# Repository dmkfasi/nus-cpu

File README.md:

# nus-cpu

This is my own yet another attempt to re-create Nintendo 64 motherboard for a portable, tablet or bartop mod.

I am going after for as much as possible: modular design, reuse of original components, cheapest production costs and the best visual display picture.

There are many bright minds out there whose ideas I try to adopt and develop further. But since I lack of expertise on several electronics topics, this whole thing definately will need some tune up.

Feel free to use, share and modify!

# Work in progress
Schematics is not verified so far, but it looks complete and legit and came from a more or less reliable source off a retrogaming community board. Everything has been broken down into following components:
* CPU-RCP defines core:
    * CPU to RCP connections;
    * RCP to PIF (Nintendo peripherials controller);
    * PIF to Controller Pak;
    * Power rails, ENABLE delay and /COLDRESET circuit, decoupling capacitors;
    * and breakout connections to external peripherial devices:
        * Gamepak port, 50pin;
        * RDRAM interface, 30pin;
        * Audio DAC, 4pin;
        * Video DAC, 10pin;
        * and Controller pak (two players), 4pin.
* RCP-RDRAM defines RAM interface:
    * Uses of two or four chips:
        * 2 of RDRAM18;
        * 4 of RDRAM18;
        * 2 of RDRAM36.
    * and onboard MX8330 clock generator;
* RCP-CART defines Gamepak interface, simple board with flat cable connector;
* RCP-SND defines audio output interface, either usage of B9480F or any other DAC and amplifier;
* RCP-VDC will define video interface.

# PCB design and production files
* CPU-RCP is 4 layer board, finished, Gerber files are included;

* RCP-RDRAM is 4 layer board, finished, Gerber files are included;

* RCP-CART is 2 layer board, finished, Gerber files are included;

* RCP-SND is not started yet;
* RCP-VDC is not started yet;

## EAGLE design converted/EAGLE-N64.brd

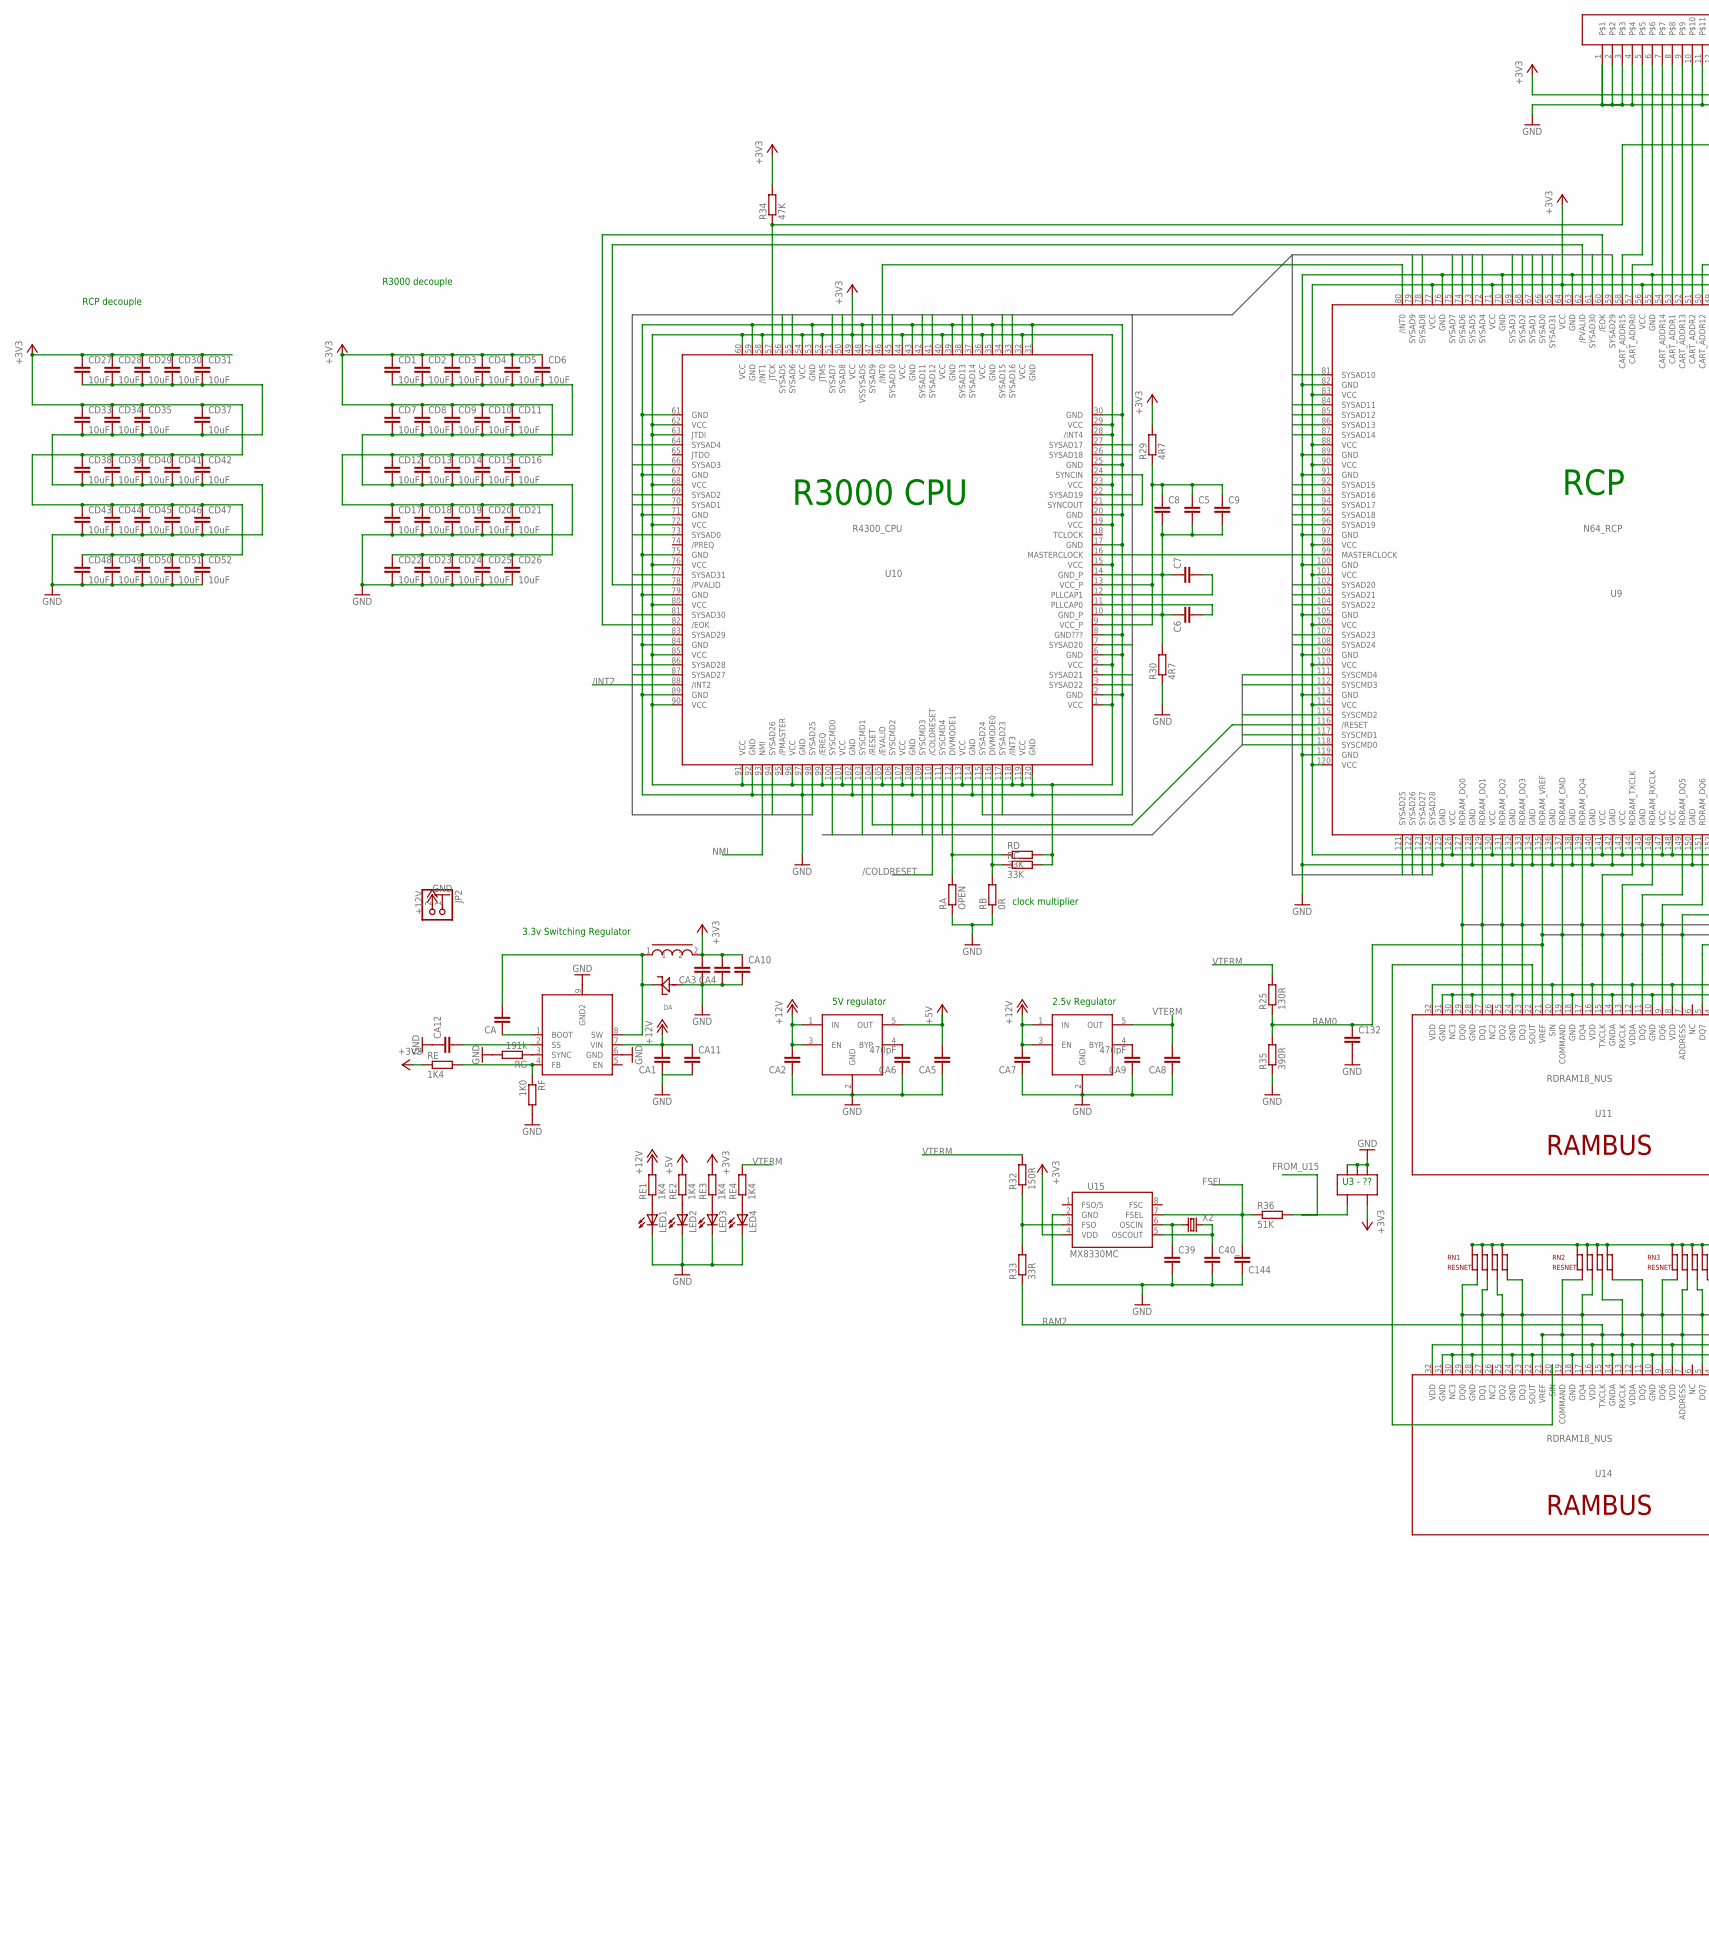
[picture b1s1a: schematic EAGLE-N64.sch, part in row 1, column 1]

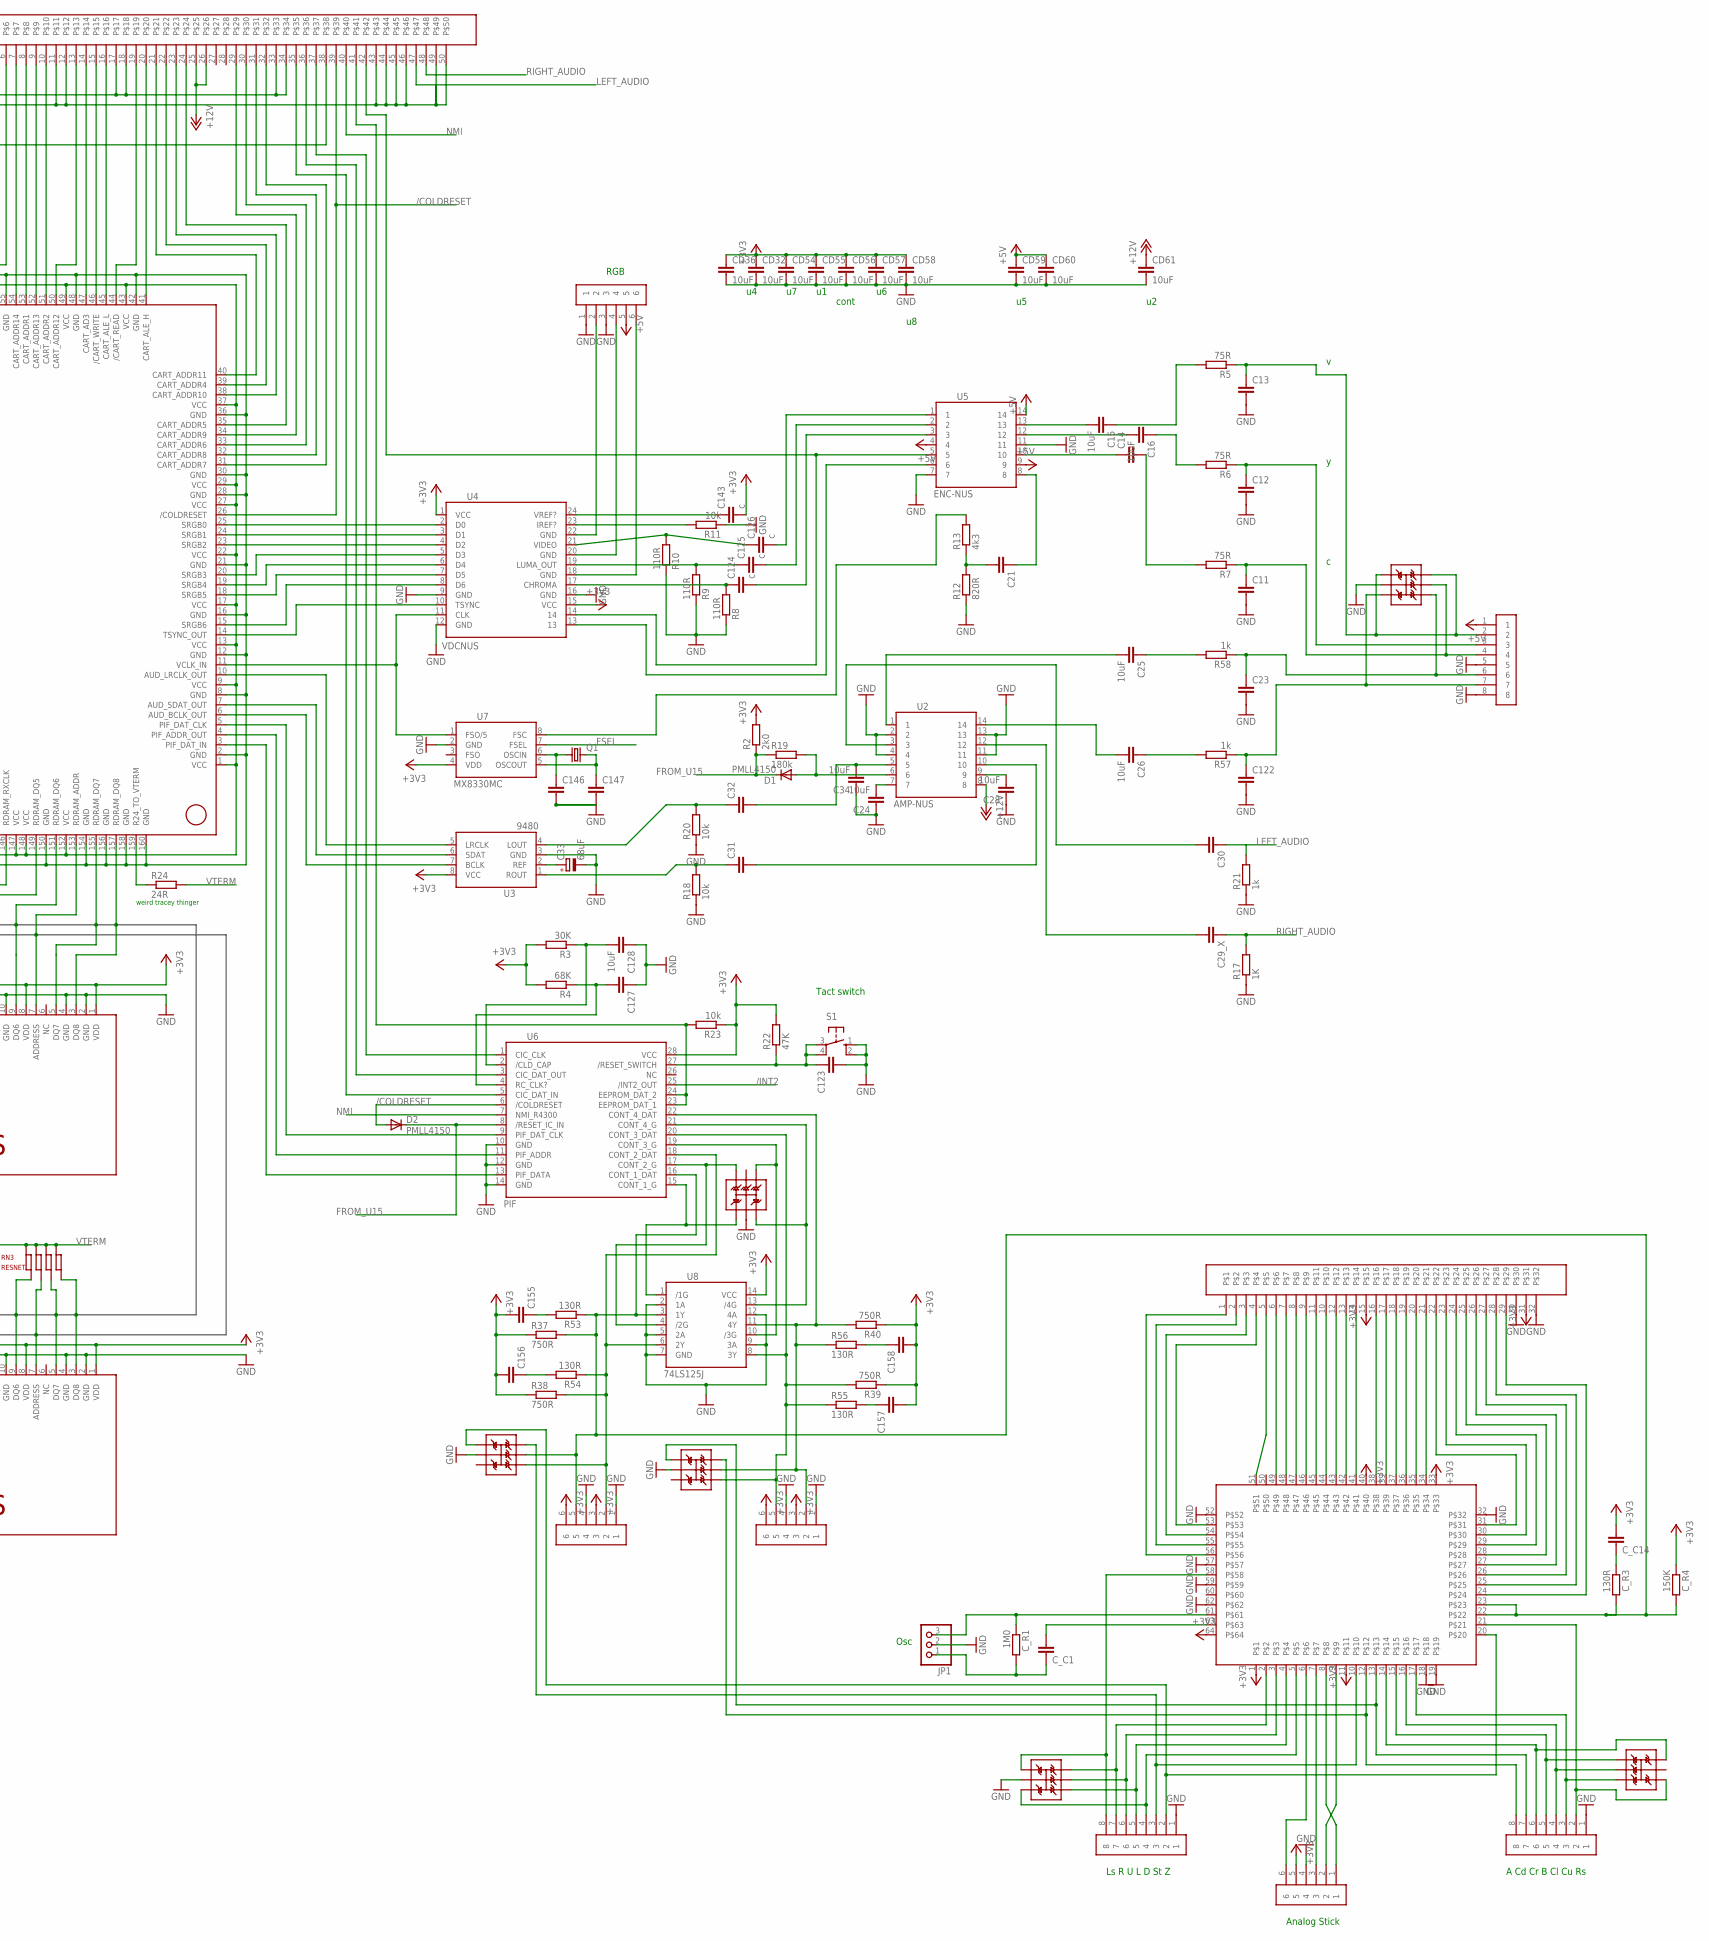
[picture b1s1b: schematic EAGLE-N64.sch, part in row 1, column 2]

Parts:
3V3: LM22680; PSOP-8
AV: PINHEAD-1X8; 2MMPINHEAD-1X8
BUTT1, BUTT2: PINHEAD-1X8; 2MMPINHEAD-1X8
C5: C-EUC0805K; C0805K
C6, C7, C8, C9, C11, C12, C13, C14, C21, C23, C29_X, C30, C31, C32, C39, C40_, C122, C123, C127, C132, C144, C146, C147, C155, C156, C157, C158: C-EUC0805; C0805
C15, C16, C24, C25, C26, C28, C34, C128: 10uF; C0805
C33: 68uF; C/6032-28R
C124, C125, C126, C143: c; C0805
CA, CA1, CA4: C-EUC1206K; C1206K
CA2, CA5, CA7, CA8, CA10, CA11, CA12: C-EUC0805K; C0805K
CA3: C-EUC1210K; C1210K
CA6, CA9: 470pF; C0805K
CD1, CD2, CD3, CD4, CD5, CD6, CD7, CD8, CD9, CD10, CD11, CD12, CD13, CD14, CD15, CD16, CD17, CD18, CD19, CD20, CD21, CD22, CD23, CD24, CD25, CD26, CD27, CD28, CD29, CD30, CD31, CD32, CD33, CD34, CD35, CD36, CD37, CD38, CD39, CD40, CD41, CD42, CD43, CD44, CD45, CD46, CD47, CD48, CD49, CD50, CD51, CD52, CD54, CD55, CD56, CD57, CD58, CD59, CD60, CD61: 10uF; C0805
CONT1, CONT2: PINHEAD-1X6; 2MMPINHEAD-1X6
C_C1, C_C14: C-EUC0805; C0805
C_R1: 1M0; M0805
C_R3: 130R; M0805
C_R4: 150K; M0805
C_U1: CNT-NUS; PQFP64
D1, D2: PMLL4150; SOD80C
DA: STKYDIODE
JOY: PINHEAD-1X6; 2MMPINHEAD-1X6
JP1: PINHD-1X3; 1X03
JP2: PINHD-1X2; 1X02
LED1, LED2, LED3, LED4: LEDCHIPLED_0805; CHIPLED_0805
Q1: CRYTALHC49S; HC49/S
R2: 2k0; M0805
R3: 30K; M0805
R4: 68K; M0805
R5, R6, R7: 75R; M0805
R8, R9, R10: 110R; M0805
R11, R18, R20, R23: 10k; M0805
R12: 820R; M0805
R13: 4k3; M0805
R17: 1K; M0805
R19: 180k; M0805
R21, R57, R58: 1k; M0805
R22, R34: 47K; M0805
R24: 24R; M0805
R25, R53, R54, R55, R56: 130R; M0805
R29, R30: 4R7; M0805
R32: 150R; M0805
R33: 33R; M0805
R35: 390R; M0805
R36: 51K; M0805
R37, R38, R39, R40: 750R; M0805
RA: OPEN; M0805
RB: 0R; M0805
RC: 33K; M0805
RD: 33K; M0805
RE, RE1, RE2, RE3, RE4: 1K4; M0805
RF: 1K0; M0805
RG: 191k; M0805
RGB: PINHEAD-1X6; 2MMPINHEAD-1X6
RN1, RN2, RN3: RESNET; RESARRAY
S1: 10-XX; B3F-10XX
TVS1, TVS2, TVS3, TVS4, TVS5, TVS6: TVS; SC-74
U2: AMP-NUS; SO14
U3: 9480; SO8
U3_: U3; SOT23-5
U4: VDCNUS; SO24
U5: ENC-NUS; SO14
U6: PIF; SO28W
U7, U15: MX8330MC; SO08
U8: 74LS125J; QSOP14
U9: N64_RCP; PQFP160
U10: R4300_CPU; QFP120
U11, U14: RDRAM18_NUS; SHP32
U12, U13: MIC5219; SOT23-5
U$37: PINHEAD-25X2
U$38: PINHEAD-16X2SMALLER; 2MMPINHEAD-16X2
U$52: INDUCTOR
X2: CRYTALHC49S; HC49/S

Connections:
3V3: C143.2, C155.2, C156.2, C157.2, C158.2, CA3.2, CA4.2, CA10.1, CD1.1, CD2.1, CD3.1, CD4.1, CD5.1, CD6.1, CD7.1, CD8.1, CD9.1, CD10.1, CD11.1, CD12.1, CD13.1, CD14.1, CD15.1, CD16.1, CD17.1, CD18.1, CD19.1, CD20.1, CD21.1, CD22.1, CD23.1, CD24.1, CD25.1, CD26.1, CD27.1, CD28.1, CD29.1, CD30.1, CD31.1, CD32.1, CD33.1, CD34.1, CD35.1, CD36.1, CD37.1, CD38.1, CD39.1, CD40.1, CD41.1, CD42.1, CD43.1, CD44.1, CD45.1, CD46.1, CD47.1, CD48.1, CD49.1, CD50.1, CD51.1, CD52.1, CD54.1, CD55.1, CD56.1, CD57.1, CD58.1, CONT1.3, CONT1.6, CONT2.3, CONT2.6, C_C14.2, C_R4.1, C_U1.1, C_U1.11, C_U1.33, C_U1.40, C_U1.64, JOY.5, R2.2, R3.2, R4.2, R22.2, R23.1, R29.2, R34.2, R37.1, R38.1, R39.1, R40.1, RC.2, RD.2, RE.1, RE3.2, U3.8 (VCC), U3_.5, U4.1 (VCC), U4.15 (VCC), U6.28 (VCC), U7.4 (VDD), U8.14 (VCC), U9.1 (VCC), U9.9 (VCC), U9.13 (VCC), U9.17 (VCC), U9.22 (VCC), U9.27 (VCC), U9.29 (VCC), U9.37 (VCC), U9.43 (VCC), U9.49 (VCC), U9.56 (VCC), U9.64 (VCC), U9.71 (VCC), U9.77 (VCC), U9.83 (VCC), U9.88 (VCC), U9.90 (VCC), U9.98 (VCC), U9.101 (VCC), U9.106 (VCC), U9.110 (VCC), U9.114 (VCC), U9.120 (VCC), U9.126 (VCC), U9.130 (VCC), U9.141 (VCC), U9.143 (VCC), U9.147 (VCC), U9.148 (VCC), U9.152 (VCC), U10.1 (VCC), U10.5 (VCC), U10.15 (VCC), U10.19 (VCC), U10.23 (VCC), U10.28 (/INT4), U10.29 (VCC), U10.32 (VCC), U10.36 (VCC), U10.40 (VCC), U10.44 (VCC), U10.49 (VCC), U10.52 (JTMS), U10.54 (VCC), U10.58 (/INT1), U10.60 (VCC), U10.62 (VCC), U10.63 (JTDI), U10.68 (VCC), U10.72 (VCC), U10.76 (VCC), U10.80 (VCC), U10.85 (VCC), U10.90 (VCC), U10.91 (VCC), U10.96 (VCC), U10.99 (/EREQ), U10.101 (VCC), U10.105 (/EVALID), U10.107 (VCC), U10.113 (VCC), U10.118 (/INT3), U10.119 (VCC), U11.1 (VDD), U11.8 (VDD), U11.12 (VDDA), U11.16 (VDD), U11.20 (SIN), U11.32 (VDD), U14.1 (VDD), U14.8 (VDD), U14.12 (VDDA), U14.16 (VDD), U14.32 (VDD), U15.4 (VDD), U$37.17, U$37.18, U$37.33, U$37.34, U$38.15, U$38.31, U$52.2
+5V: AV.1, CA5.2, CD59.1, CD60.1, RE2.2, RGB.5, U5.4, U5.9, U5.14, U13.5 (OUT)
+12V: 3V3.7 (VIN), CA1.2, CA2.2, CA7.2, CA11.1, CD61.1, JP2.2, RE1.2, U2.8, U12.1 (IN), U12.3 (EN), U13.1 (IN), U13.3 (EN), U$37.25, U$37.26
/COLDRESET: D2.A, U6.6 (/COLDRESET), U9.26 (/COLDRESET), U10.110 (/COLDRESET), U$37.39
/INT2: U6.25 (/INT2_OUT), U10.88 (/INT2)
ADJ: 3V3.4 (FB), RE.2, RF.1
C16X: C16.1, R6.2
C_C11: C_C1.1, C_R1.2, JP1.1
DQ0: RN1.1, U9.127 (RDRAM_DQ0), U11.29 (DQ0), U14.29 (DQ0)
DQ1: RN1.2, U9.129 (RDRAM_DQ1), U11.27 (DQ1), U14.27 (DQ1)
DQ2: RN1.3, U9.131 (RDRAM_DQ2), U11.25 (DQ2), U14.25 (DQ2)
DQ3: RN1.4, U9.133 (RDRAM_DQ3), U11.23 (DQ3), U14.23 (DQ3)
DQ4: RN2.2, U9.139 (RDRAM_DQ4), U11.17 (DQ4), U14.17 (DQ4)
DQ5: RN2.4, U9.149 (RDRAM_DQ5), U11.11 (DQ5), U14.11 (DQ5)
DQ6: RN3.1, U9.151 (RDRAM_DQ6), U11.9 (DQ6), U14.9 (DQ6)
DQ7: RN3.3, U9.155 (RDRAM_DQ7), U11.5 (DQ7), U14.5 (DQ7)
DQ8: RN3.4, U9.157 (RDRAM_DQ8), U11.3 (DQ8), U14.3 (DQ8)
FROM_U15: D1.C, D2.C, R2.1, R19.1, R36.2, U3_.4, U6.8 (/RESET_IC_IN)
FSEL: C144.2, R36.1, U7.7 (FSEL), U15.7 (FSEL)
FSO1: R32.1, R33.2, U15.3 (FSO)
GND: 3V3.6 (GND), 3V3.9 (GND2), AV.5, AV.8, BUTT1.1, BUTT2.1, C11.2, C12.2, C13.2, C23.2, C24.1, C28.1, C33.-, C34.1, C39.2, C40_.2, C122.2, C123.2, C127.1, C128.1, C132.2, C144.1, C146.2, C147.2, CA1.1, CA2.1, CA3.1, CA4.1, CA5.1, CA6.1, CA7.1, CA8.1, CA9.1, CA10.2, CA11.2, CA12.1, CD1.2, CD2.2, CD3.2, CD4.2, CD5.2, CD6.2, CD7.2, CD8.2, CD9.2, CD10.2, CD11.2, CD12.2, CD13.2, CD14.2, CD15.2, CD16.2, CD17.2, CD18.2, CD19.2, CD20.2, CD21.2, CD22.2, CD23.2, CD24.2, CD25.2, CD26.2, CD27.2, CD28.2, CD29.2, CD30.2, CD31.2, CD32.2, CD33.2, CD34.2, CD35.2, CD36.2, CD37.2, CD38.2, CD39.2, CD40.2, CD41.2, CD42.2, CD43.2, CD44.2, CD45.2, CD46.2, CD47.2, CD48.2, CD49.2, CD50.2, CD51.2, CD52.2, CD54.2, CD55.2, CD56.2, CD57.2, CD58.2, CD59.2, CD60.2, CD61.2, CONT1.1, CONT1.4, CONT2.1, CONT2.4, C_U1.18, C_U1.19, C_U1.32, C_U1.52, C_U1.57, C_U1.59, C_U1.62, DA.+, JOY.4, JP1.2, JP2.1, LED1.C, LED2.C, LED3.C, LED4.C, R8.1, R9.1, R10.1, R11.1, R12.1, R17.1, R18.1, R20.1, R21.1, R30.1, R35.1, RA.1, RB.1, RF.2, RG.2, RGB.1, RGB.3, S1.1 (S), S1.2 (S1), TVS1.2, TVS2.2, TVS3.2, TVS4.2, TVS5.2, U2.2, U2.4, U2.11, U2.13, U3.3 (GND), U3_.1, U3_.2, U3_.3, U4.9 (GND), U4.12 (GND), U4.16 (GND), U5.7, U5.11, U6.10 (GND), U6.12 (GND), U6.14 (GND), U7.2 (GND), U8.2 (1A), U8.5 (2A), U8.7 (GND), U8.9 (3A), U8.12 (4A), U9.2 (GND), U9.8 (GND), U9.12 (GND), U9.16 (GND), U9.21 (GND), U9.28 (GND), U9.30 (GND), U9.36 (GND), U9.42 (GND), U9.48 (GND), U9.55 (GND), U9.63 (GND), U9.70 (GND), U9.76 (GND), U9.82 (GND), U9.89 (GND), U9.91 (GND), U9.97 (GND), U9.100 (GND), U9.105 (GND), U9.109 (GND), U9.113 (GND), U9.119 (GND), U9.125 (GND), U9.128 (GND), U9.132 (GND), U9.134 (GND), U9.136 (GND), U9.138 (GND)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
INT0: U9.80 (/INT0), U10.46 (/INT0)
LEFT_AUDIO: C30.1, R21.2, U$37.47
unnamed: C156.1, R54.2
unnamed: C155.1, R53.2
unnamed: U4.11 (CLK), U7.1 (FSO/5), U9.11 (VCLK_IN)
unnamed: R24.1, U9.159 (R24_TO_VTERM)
unnamed: C147.1, Q1.2, U7.5 (OSCOUT)
unnamed: C146.1, Q1.1, U7.6 (OSCIN)
unnamed: BUTT1.2, C_U1.20, TVS3.1
unnamed: RGB.2, U4.22 (GND)
unnamed: RGB.4, U4.20 (GND)
unnamed: U6.9 (PIF_DAT_CLK), U9.5 (PIF_DAT_CLK)
unnamed: U6.11 (PIF_ADDR), U9.4 (PIF_ADDR_OUT)
unnamed: U6.13 (PIF_DATA), U9.3 (PIF_DAT_IN)
unnamed: TVS2.1, U6.15 (CONT_1_G), U8.1 (/1G)
unnamed: CONT1.5, C_R3.2, C_R4.2, C_U1.22, C_U1.23, R37.2, R53.1, TVS3.5, U6.16 (CONT_1_DAT), U8.3 (1Y)
unnamed: BUTT1.3, C_U1.10, TVS3.6
unnamed: LED1.A, RE1.1
unnamed: CONT1.2, R38.2, R54.1, TVS3.4, U6.18 (CONT_2_DAT), U8.6 (2Y)
unnamed: TVS2.4, U6.19 (CONT_3_G), U8.10 (/3G)
unnamed: CONT2.5, R39.2, R55.1, TVS4.4, U6.20 (CONT_3_DAT), U8.8 (3Y)
unnamed: TVS2.3, U6.21 (CONT_4_G), U8.13 (/4G)
unnamed: CONT2.2, R40.2, R56.1, TVS4.5, U6.22 (CONT_4_DAT), U8.11 (4Y)
unnamed: U4.2 (D0), U9.25 (SRGB0)
unnamed: U9.116 (/RESET), U10.104 (/RESET)
unnamed: TVS2.6, U6.17 (CONT_2_G), U8.4 (/2G)
unnamed: U9.62 (/PVALID), U10.78 (/PVALID)
unnamed: U9.60 (/EOK), U10.82 (/EOK)
unnamed: C123.1, R22.1, S1.3, S1.4 (P1), U6.27 (/RESET_SWITCH)
unnamed: U4.3 (D1), U9.24 (SRGB1)
unnamed: RB.2, RC.1, U10.116 (DIVMODE0)
unnamed: U9.39 (CART_ADDR4), U$37.22
unnamed: RA.2, RD.1, U10.112 (DIVMODE1)
unnamed: U9.58 (CART_ADDR15), U$37.5
unnamed: U9.57 (CART_ADDR0), U$37.6
unnamed: U9.54 (CART_ADDR14), U$37.7
unnamed: U9.53 (CART_ADDR1), U$37.8
unnamed: U9.52 (CART_ADDR13), U$37.9
unnamed: U9.51 (CART_ADDR2), U$37.10
unnamed: U9.99 (MASTERCLOCK), U10.16 (MASTERCLOCK)
unnamed: U9.50 (CART_ADDR12), U$37.13
unnamed: U9.47 (CART_AD3), U$37.14
unnamed: U9.46 (/CART_WRITE), U$37.15
unnamed: U9.45 (CART_ALE_L), U$37.16
unnamed: U9.44 (/CART_READ), U$37.19
unnamed: U9.41 (CART_ALE_H), U$37.20
unnamed: U9.38 (CART_ADDR10), U$37.23
unnamed: U9.35 (CART_ADDR5), U$37.24
unnamed: U9.34 (CART_ADDR9), U$37.29
unnamed: U9.33 (CART_ADDR6), U$37.30
unnamed: U9.32 (CART_ADDR8), U$37.31
unnamed: U9.31 (CART_ADDR7), U$37.32
unnamed: C157.1, R55.2
unnamed: U6.5 (CIC_DAT_IN), U$37.35
unnamed: U6.3 (CIC_DAT_OUT), U$37.36
unnamed: U6.1 (CIC_CLK), U$37.37
unnamed: R23.2, U6.23 (EEPROM_DAT_1), U6.24 (EEPROM_DAT_2), U$37.41
unnamed: C5.1, C8.1, C9.1, R29.1, U10.9 (VCC_P), U10.13 (VCC_P)
unnamed: C5.2, C6.1, C7.1, C8.2, C9.2, R30.2, U10.10 (GND_P), U10.14 (GND_P)
unnamed: C6.2, U10.11 (PLLCAP0)
unnamed: C7.2, U10.12 (PLLCAP1)
unnamed: U10.21 (SYNCOUT), U10.24 (SYNCIN)
unnamed: U3.5 (LRCLK), U9.10 (AUD_LRCLK_OUT)
unnamed: U3.6 (SDAT), U9.7 (AUD_SDAT_OUT)
unnamed: U3.7 (BCLK), U9.6 (AUD_BCLK_OUT)
unnamed: C33.+, U3.2 (REF)
unnamed: C127.2, R4.1, U6.4 (RC_CLK?)
unnamed: C128.2, R3.1, U6.2 (/CLD_CAP)
unnamed: U4.4 (D2), U9.23 (SRGB2)
unnamed: U4.5 (D3), U9.20 (SRGB3)
unnamed: U4.6 (D4), U9.19 (SRGB4)
unnamed: U4.7 (D5), U9.18 (SRGB5)
unnamed: U4.8 (D6), U9.15 (SRGB6)
unnamed: U4.10 (TSYNC), U9.14 (TSYNC_OUT)
unnamed: R11.2, U4.23 (IREF?)
unnamed: C126.1, R10.2, U4.21 (VIDEO)
unnamed: R34.1, U10.57 (JTCK), U$37.38
unnamed: C32.1, R20.2, U3.4 (LOUT)
unnamed: C31.1, R18.2, U3.1 (ROUT)
unnamed: C143.1, U4.24 (VREF?)
unnamed: C125.1, R9.2, U4.19 (LUMA_OUT)
unnamed: C124.1, R8.2, U4.17 (CHROMA)
unnamed: C158.1, R56.2
unnamed: C32.2, C34.2, U2.5
unnamed: C31.2, U2.10
unnamed: C24.2, U2.7
unnamed: C28.2, U2.9
unnamed: C29_X.2, U2.12
unnamed: C30.2, U2.3
unnamed: D1.A, R19.2, U2.6
unnamed: C25.1, R58.2
unnamed: C14.1, U5.10
unnamed: C26.2, U2.14
unnamed: AV.7, C122.1, R57.1, TVS1.3
unnamed: C26.1, R57.2
unnamed: C_U1.56, U$38.1
unnamed: CA6.2, U13.4 (BYP)
unnamed: C_U1.55, U$38.2
unnamed: U4.13, U5.6
unnamed: U4.14, U5.5, U$37.42
unnamed: C124.2, U5.3
unnamed: C125.2, U5.2
unnamed: C126.2, U5.1
unnamed: C15.1, R5.2
unnamed: C15.2, U5.13
unnamed: C16.2, U5.12
unnamed: AV.4, C11.1, R7.1, TVS1.5
unnamed: AV.3, C12.1, R6.1
unnamed: C14.2, R7.2
unnamed: C21.1, U5.8
unnamed: R13.2, U7.8 (FSC)
unnamed: C21.2, R12.2, R13.1
unnamed: AV.2, C13.1, R5.1, TVS1.1, TVS1.6
unnamed: RGB.6, U4.18 (GND)
unnamed: C_U1.8, JOY.1
unnamed: C_U1.54, U$38.3
unnamed: C_U1.53, U$38.4
unnamed: C_U1.9, JOY.2
unnamed: C_U1.51, U$38.5
unnamed: C_U1.49, U$38.6
unnamed: C_U1.48, U$38.7
unnamed: C_U1.47, U$38.8
unnamed: U9.40 (CART_ADDR11), U$37.21
unnamed: C_U1.46, U$38.9
unnamed: C_U1.45, U$38.11
unnamed: C_U1.44, U$38.10
unnamed: C_U1.43, U$38.12
unnamed: C_U1.42, U$38.13
unnamed: C_U1.41, U$38.14
unnamed: BUTT2.2, C_U1.21, TVS6.1
unnamed: C_U1.38, U$38.16
unnamed: C_U1.37, U$38.18
unnamed: C_U1.39, U$38.17
unnamed: C_U1.36, U$38.19
unnamed: C_U1.35, U$38.20
unnamed: C_U1.34, U$38.21
unnamed: C_U1.31, U$38.22
unnamed: C_U1.30, U$38.23
unnamed: C_U1.29, U$38.24
unnamed: C_U1.28, U$38.25
unnamed: C_U1.27, U$38.26
unnamed: C_U1.26, U$38.27
unnamed: C_U1.25, U$38.28
unnamed: C_U1.24, U$38.29
unnamed: C_C14.1, C_R3.1
unnamed: 3V3.2 (SS), CA12.2
unnamed: BUTT2.3, C_U1.17, TVS6.6
unnamed: BUTT2.4, C_U1.16, TVS6.5
unnamed: BUTT2.5, C_U1.15, TVS6.4
unnamed: BUTT2.6, C_U1.14, TVS6.3
unnamed: BUTT2.7, C_U1.13, TVS4.1
unnamed: BUTT2.8, C_U1.12, TVS4.6
unnamed: C_U1.7, JOY.3
unnamed: C_U1.6, JOY.6
unnamed: BUTT1.4, C_U1.5, TVS5.3
unnamed: BUTT1.5, C_U1.4, TVS5.4
unnamed: BUTT1.6, C_U1.3, TVS5.5
unnamed: BUTT1.7, C_U1.2, TVS5.6
unnamed: BUTT1.8, C_U1.58, TVS5.1
unnamed: C_R1.1, C_U1.61, JP1.3
unnamed: C_C1.2, C_U1.63
unnamed: CA9.2, U12.4 (BYP)
unnamed: 3V3.3 (SYNC), RG.1
unnamed: 3V3.1 (BOOT), CA.1
unnamed: LED2.A, RE2.1
unnamed: LED4.A, RE4.1
unnamed: LED3.A, RE3.1
NMI: U6.7 (NMI_R4300), U10.93 (NMI), U$37.40
OSCIN1: C39.1, U15.6 (OSCIN), X2.1
OSCOUT1: C40_.1, U15.5 (OSCOUT), X2.2
R58: AV.6, C23.1, R58.1, TVS1.4
RAM0: C132.1, R25.1, R35.2, U9.135 (RDRAM_VREF), U11.21 (VREF), U14.21 (VREF)
RAM1: RN2.1, U9.137 (RDRAM_CMD), U11.19 (COMMAND), U14.19 (COMMAND)
RAM2: R33.1, U9.144 (RDRAM_TXCLK), U11.15 (TXCLK), U14.15 (TXCLK)
RAM3: RN2.3, U9.146 (RDRAM_RXCLK), U11.13 (RXCLK), U14.13 (RXCLK)
RAM4: RN3.2, U9.153 (RDRAM_ADDR), U11.7 (ADDRESS), U14.7 (ADDRESS)
RIGHT_AUDIO: C29_X.1, R17.2, U$37.48
SW: 3V3.8 (SW), CA.2, DA.-, U$52.1
SYSAD0: U9.66 (SYSAD0), U10.73 (SYSAD0)
SYSAD1: U9.67 (SYSAD1), U10.70 (SYSAD1)
SYSAD2: U9.68 (SYSAD2), U10.69 (SYSAD2)
SYSAD3: U9.69 (SYSAD3), U10.66 (SYSAD3)
SYSAD4: U9.72 (SYSAD4), U10.64 (SYSAD4)
SYSAD5: U9.73 (SYSAD5), U10.56 (SYSAD5)
SYSAD6: U9.74 (SYSAD6), U10.55 (SYSAD6)
SYSAD7: U9.75 (SYSAD7), U10.51 (SYSAD7)
SYSAD8: U9.78 (SYSAD8), U10.50 (SYSAD8)
SYSAD9: U9.79 (SYSAD9), U10.47 (SYSAD9)
SYSAD10: U9.81 (SYSAD10), U10.45 (SYSAD10)
SYSAD11: U9.84 (SYSAD11), U10.42 (SYSAD11)
SYSAD12: U9.85 (SYSAD12), U10.41 (SYSAD12)
SYSAD13: U9.86 (SYSAD13), U10.38 (SYSAD13)
SYSAD14: U9.87 (SYSAD14), U10.37 (SYSAD14)
SYSAD15: U9.92 (SYSAD15), U10.34 (SYSAD15)
SYSAD16: U9.93 (SYSAD16), U10.33 (SYSAD16)
SYSAD17: U9.94 (SYSAD17), U10.27 (SYSAD17)
SYSAD18: U9.95 (SYSAD18), U10.26 (SYSAD18)
SYSAD19: U9.96 (SYSAD19), U10.22 (SYSAD19)
SYSAD20: U9.102 (SYSAD20), U10.7 (SYSAD20)
SYSAD21: U9.103 (SYSAD21), U10.4 (SYSAD21)
SYSAD22: U9.104 (SYSAD22), U10.3 (SYSAD22)
SYSAD23: U9.107 (SYSAD23), U10.117 (SYSAD23)
SYSAD24: U9.108 (SYSAD24), U10.115 (SYSAD24)
SYSAD25: U9.121 (SYSAD25), U10.98 (SYSAD25)
SYSAD26: U9.122 (SYSAD26), U10.94 (SYSAD26)
SYSAD27: U9.123 (SYSAD27), U10.87 (SYSAD27)
SYSAD28: U9.124 (SYSAD28), U10.86 (SYSAD28)
SYSAD29: U9.59 (SYSAD29), U10.83 (SYSAD29)
SYSAD30: U9.61 (SYSAD30), U10.81 (SYSAD30)
SYSAD31: U9.65 (SYSAD31), U10.77 (SYSAD31)
SYSCMD0: U9.118 (SYSCMD0), U10.100 (SYSCMD0)
SYSCMD1: U9.117 (SYSCMD1), U10.103 (SYSCMD1)
SYSCMD2: U9.115 (SYSCMD2), U10.106 (SYSCMD2)
SYSCMD3: U9.112 (SYSCMD3), U10.109 (SYSCMD3)
SYSCMD4: U9.111 (SYSCMD4), U10.111 (SYSCMD4)
U2: C25.2, U2.1
U3: U11.22 (SOUT), U14.20 (SIN)
VTERM: CA8.2, R24.2, R25.2, R32.2, RE4.2, RN1.5, RN1.6, RN1.7, RN1.8, RN2.5, RN2.6, RN2.7, RN2.8, RN3.5, RN3.6, RN3.7, RN3.8, U12.5 (OUT)

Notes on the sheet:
clock multiplier
R3000 CPU
RCP
weird tracey thinger
5V regulator
2.5v Regulator
3.3v Switching Regulator
U3 - ??
RGB
Ls R U L D St Z
A Cd Cr B Cl Cu Rs
Analog Stick
Osc
Tact switch
R3000 decouple
RCP decouple
cont

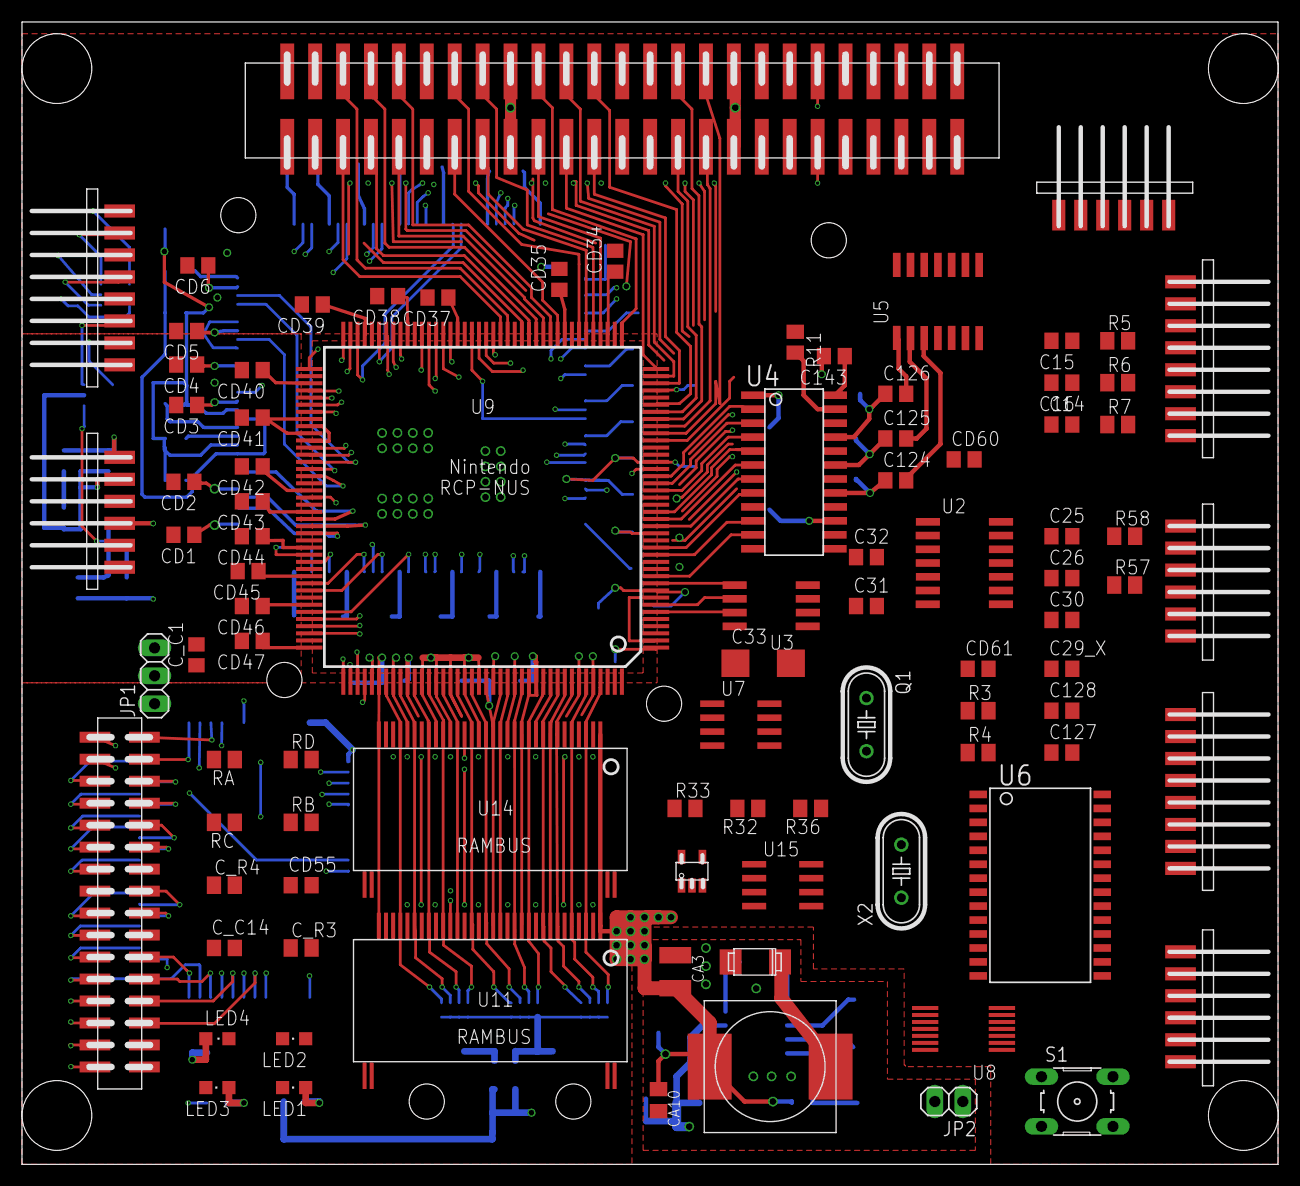
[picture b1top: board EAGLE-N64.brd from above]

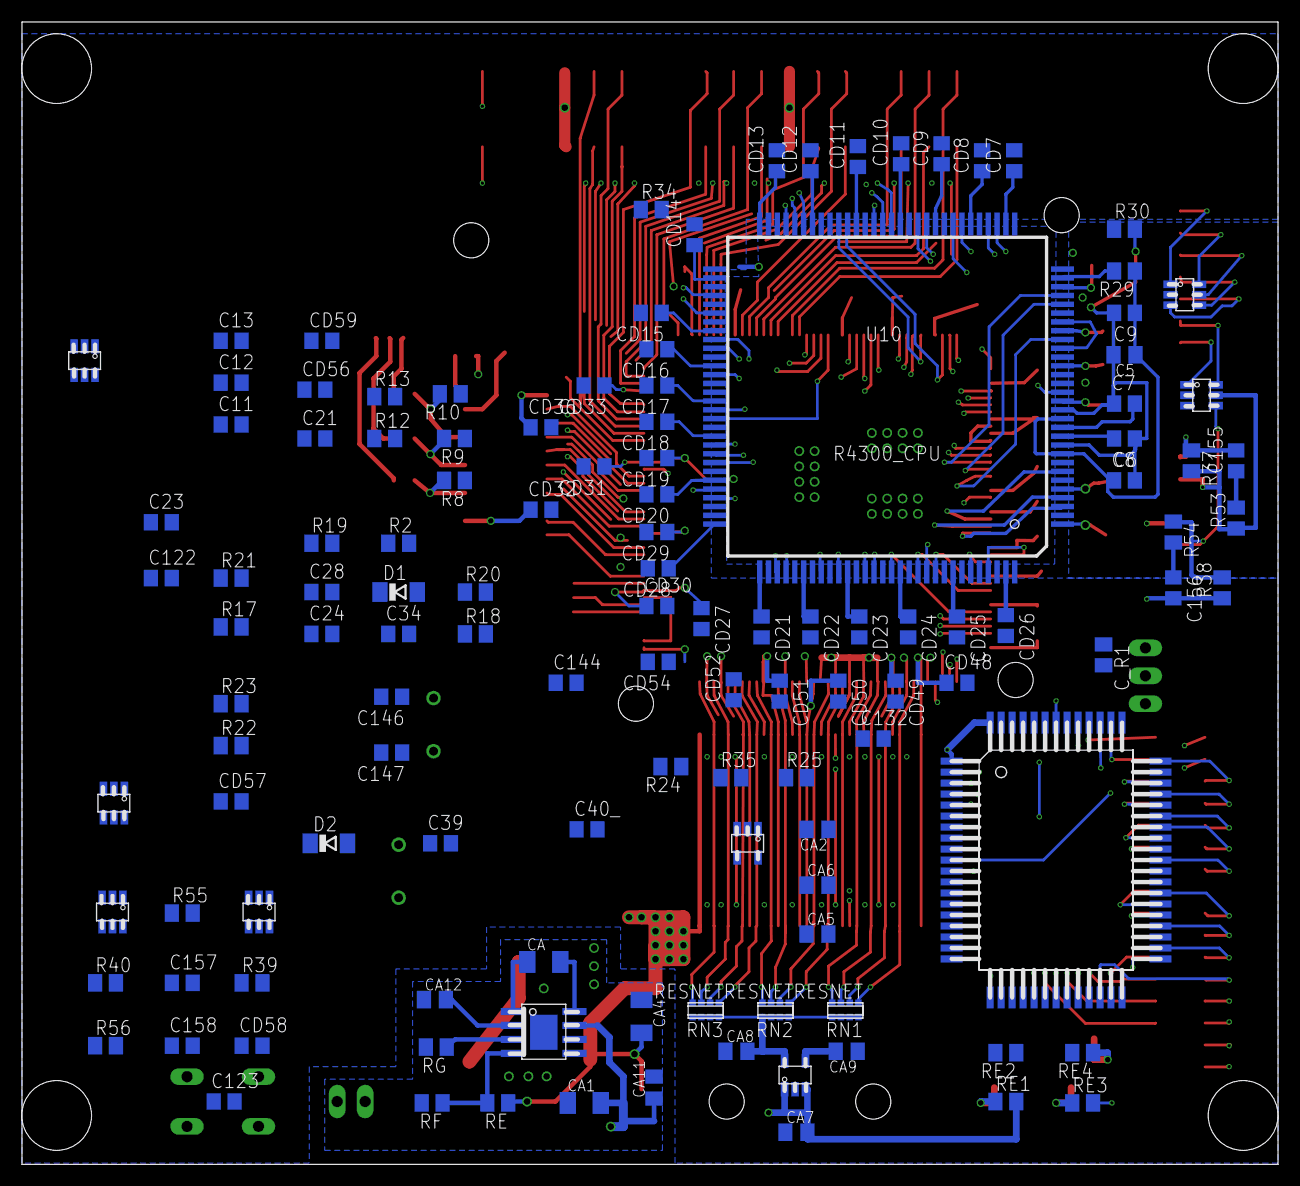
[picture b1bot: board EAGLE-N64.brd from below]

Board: 4 copper layers, 114.3 x 103.9 mm, 216 parts (125 on the bottom side), 239 nets.

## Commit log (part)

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2017-01-15 Playing around
2017-01-16 Amphenol FCI 62684-50110E9ALF, flat cable connector for CART EDGE, 50pins, 0.5mm pitch
2017-01-18 Design Rules setting changed to fit better board and fab process
2017-01-18 Shortened pin counter
2017-01-18 Fixed RESNET pinout to match current footprint of CAY16-J4
2017-01-18 Redo signal termination (a major fail here), power supply lines, going to rewire for 0.1524mm (8mil) line clearance
2017-01-18 Get rid of outdated files
2017-01-19 Moved for more appropriate naming scheme
2017-01-19 Get back to 0.2mm line space Design Rule
2017-01-19 Board changed to L-shape, moved top side RDRAM chips to trick difficult to connect SOUT pin, rewired VREF resistor devider, other improvements
2017-01-20 This image turned out to be -05-1 revision with MAV-NUS video DAC
2017-01-20 Dimensions added, capacitors moved around, getting ready to shrink the board
2017-01-20 Revision 2, mostly finished, TODO: checks
2017-01-20 Text size reduced
2017-01-20 More stitchings for VREF line, minor text cleanups
2017-01-21 Minor cleanups
2017-01-22 PDF doc reference added
2017-01-22 Redrawn with actual connector size, mounting holes and outlines
2017-01-22 Useless
2017-01-22 More convenient node name for better bash navigation
2017-01-22 OSH Park PCB images designed by Michael Chen
2017-01-22 AMPHENOL flat cable 50 pin 0.5mm pitch for connecting CART EDGE
2017-01-22 Well, it actually revision 08 and not 05
2017-01-22 Cleaning up
2017-01-22 Cleanup
2017-01-22 Changed DC input capacitors to 1206 size
2017-01-22 Footprints updated, using AMP connector for CART EDGE now
2017-01-22 Mixed up fab name
2017-01-22 Footprints updated
2017-01-22 Wizard generated 4 pins 1.0mm pitch FPC for audio
2017-01-22 New name for CART EDGE breakout connector
2017-01-22 Accidently renamed, gotta rid of it
2017-01-22 Dedicated PIF-NUS footprint
2017-01-22 Removed Dwgs.User
2017-01-23 Old stuff
2017-01-24 Corrected Fab name
2017-01-24 Now using Hirose DF13 1.25mm pitch SMT connector for power input
2017-01-24 Still playing around
2017-01-24 Fixed CART EDGE connector foorprint, replaced VIDEO OUT with Hirose DF52, the same type as AUDIO OUT
2017-01-26 Molex 50 pins 0.5mm pitch for CART EDGE connector
2017-01-26 Re-assigned FPC connectors, now using unified Molex 505110 series, see datasheet for details
2017-01-26 Molex FPC 505110 series, 0.5mm pitch
2017-01-26 Files cleanup
2017-01-26 Molex 502790 series 50 pins 0.5mm pitch to hook CART EDGE
2017-01-29 Filename corrected
2017-01-29 Power supply mating 02x03 pins, 2.0mm pitch
2017-01-29 Molex power input jack
2017-01-29 3D shape, exported from official STEP with FreeCAD
2017-01-29 Using new foorprints
2017-01-29 3D shapes for all the Molex connectors used
2017-01-29 3D shapes added and scaled
2017-01-29 Now using Molex 3D shapes
2017-01-31 Current netlist has been read
2017-01-31 PIF added
2017-01-31 External connections sheet added
2017-01-31 Current settings
2017-01-31 PIF-NUS redrawn for better pinout, changes to CARTEDGE for PIF connections, PushButton for RESET added
2017-01-31 CARTEDGE PIF-CIC connection changes, PIF connector removed
2017-01-31 #COLDRESET D2 diode down to ENABLE signal added
2017-02-05 Modified RDRAM EDGE for better VREF, VTERM and 3V3 pinout
2017-02-05 Now using modified RDRAM EDGE pinout
2017-02-05 Better fit of VREF Resistor divider using new RDRAM EDGE pinout, some other small improvements related to the power rails
2017-02-05 Now using new RDRAM EDGE. RDRAM EDGE moved to external connections sheet
2017-02-05 Slightly adjusted with new RDRAM EDGE footprints
2017-02-05 Better footprint layout for M50-3001545
2017-02-16 Prelimary 3D shape for RDRAM chip SHP-32 package, FreeCAD source file
2017-02-16 Preliminary 3D shape for RDRAM chip SHP-32 package, FreeCAD source file
2017-02-17 RDRAM 3D shape added on adjusted scale
2017-02-18 Adjusted scale to correct value of 0.3937
2017-02-18 RDRAM 3D shape
2017-02-19 Slightly modified pads clearance, according to actual measurements
2017-02-19 All the pads were shortened according to datasheet specs, to save PCB space as well
2017-02-19 Updated look with RDRAM chip rendered
2017-02-19 Board mechanical layout
2017-02-19 Color coated
2017-02-19 FreeCAD file out of STP, painted
2017-02-19 Moved to appropriate directory
2017-02-19 RDRAM EDGE 3D shape
2017-02-19 Colors coated
2017-02-19 Updated look
2017-02-19 Updated with RDRAM EDGE 3D shape
2017-02-19 Converted from STP
2017-02-19 Mating SMT connector for Main PCB RDRAM EDGE
2017-02-19 Correct naming scheme
2017-02-19 Mating profiles reference
2017-02-19 Fully rendered, finally. TODO coat with proper colors
2017-02-19 Fixed disappearing after export to VRML
2017-02-21 Colorized
2017-02-21 Better colorization
2017-02-21 3D shape position adjusted
2017-02-21 Moving around
2017-02-21 Rebuild to utilize new 3D shapes
2017-02-21 Future reference for RCP-NUS QFP-160 package 3D shape recreation
2017-02-21 Pin designators added on the back silkscreen
2017-02-21 Adjusted 3D shape angle and offset
2017-02-21 Changed footprint for RDRAM EDGE to m50-3601542
2017-02-22 Mechanical design reference for QFP-160 3D shape
2017-02-22 Got rid in flavor of PDFs under datasheet folder
2017-02-22 Harwin M50-3601542 footprint for RDRAM EDGE at CPU-RCP board side
2017-02-22 RDRAM EDGE SMT for CPU-RCP board side
2017-02-23 Pin size and body offset adjusted
2017-02-23 RCP-NUS 3D shape
2017-02-24 Completed 3D shape for RCP-NUS
2017-02-24 Complete FreeCAD model for RCP-NUS QFP-160
2017-02-24 Accumulated all 3D shapes for local storage
2017-02-24 Replaced duplicate footprint
2017-02-24 QFP-64 14x20mm footprint reference for CNT-NUS
2017-02-25 Rephrased a little
2017-03-02 Laying around, WIP
2017-03-02 Changed decoupler capacitors footprints to 0603 size
2017-08-17 N64 portable PCB designs by Marshall
2017-08-17 Moved to apropriate place
2017-08-17 Reduced number of decoupling capacitors for both CPU and RCP
2017-08-17 Cleanups for less decoupler capacitors
2017-08-17 Cleanups for current setup
2017-08-18 Local 3D shape copy for solid PCB 3D view
2017-08-18 Removed extra outlines
2017-08-18 Corrected model for proper 3D display
2017-08-18 Adjusted to local 3D shape copies for consistent 3D view
2017-08-18 Slight adjustments
2017-08-18 Local copy
2017-08-18 Slightly corrected
2017-08-19 Moved folder to the new name
2017-08-19 Corrected 3D shape to a local copy
2017-08-19 Corrected 3D shape to a local copy with proper size
2017-08-19 Work in progress
2017-08-19 Renamed folder
2017-08-19 Moved to Schematics folder
2017-08-20 Background fill for LC125
2017-08-20 Local copy 3 pin SMT pads
2017-08-20 Joystick interface added
2017-08-20 Local copy, BAC54 used as reference
2017-08-20 Updated 3D shape with local copy
2017-08-20 Minor updates
2017-08-20 Work in progress, updated 3D shapes
2017-08-20 3D shapes local copy
2017-08-20 VTERM decouple capacitors added
2017-08-20 Changes to decoupler capacitor quantity and nets
2017-08-20 Digital Video Clock singal moved closer
2017-08-21 Output filter for Audio DAC added
2017-08-21 Hard link library for any project settings
2017-08-21 Design Rules set according to my Fab House, switching to 4 layer board
2017-08-21 Hard link for N64 lib
2017-08-21 Initial board layout
2017-08-21 Initial project settings
2017-08-21 Peripherial copy, todo: remove extra circuits
2017-08-21 New initial schematics for DAC and Amplifier section
2017-08-21 Audio DAC moved to a separate project
2017-08-21 Auto libs changes
2017-08-21 Libname adjusted to a local hardlink copy
2017-08-21 New Design Rules for my Fab, inner power layers added
2017-08-22 Removed Audio DAC
2017-08-22 Corrected Audio Out for Digital interfacing
2017-08-22 Corrected marshallh name
2017-08-22 Temperature monitoring
2017-08-24 Power consumption measurements notes added
2017-08-24 Proper folder name
2017-08-24 Renamed to PCB-Designs
2017-08-24 Another power supply board
2017-08-24 U3 added for soft-start feature
2017-08-24 PLL capacitors size corrected
2017-08-25 MX8330 footprint, named after datasheet suggestion
2017-08-25 Remade to SOP-8
2017-08-25 VTERM/VREF current measurements commented
2017-08-25 This contains more or less modern IC
2017-08-25 It looks like correct U3 chip, NUS-CPU-04 reads 2870 on the IC body
2017-08-25 Renamed
2017-08-25 Unused so far
2017-08-25 VDC-NUS
2017-08-25 Riddance in favour of pif-nus-so-28w
2017-08-25 Adjusted and confirmed to fit actual ICs
2017-08-25 Adjusted according datasheet, TODO: confirm with real IC
2017-08-25 Slight adjustments, WIP
2017-08-26 Unused
2017-08-26 Moved to MX8300-U5
2017-08-26 Corrected and verified against real CPU
2017-08-26 Slight changes
2017-08-26 Reference field fixed
2017-08-26 Renamed to pqfp-64
2017-08-26 Preliminary 3D shape
2017-08-26 CNT-NUS 3D shape source, WIP
2017-08-27 Corrected to fit freshly created 3D shape
2017-08-27 Source file for PQFP-64 package, completed
2017-08-27 Riddance of old stuff
2017-08-27 Slight re-arrangements
2017-08-27 Re-arranged, rewired, changed sizes and renamed decoupling capacitors
2017-08-27 Newer version according to modified schematics, need slight updates on Silk Screen
2017-08-28 Solder switch for RDRAM board
2017-08-28 Notes added
2017-08-28 4 layers WIP
2017-08-28 Finished 4 layer board
2017-08-28 Finished 4 layer board with Gerber output settings
2017-08-28 Updated design rules
2017-08-28 Updated design rules for better fab pricing, corrected to comply DRC
2017-08-29 R36 and C144 moved here for ENABLE signal
2017-08-29 R36 and C144 moved from here
2017-08-29 Changed to symlink instead
2017-08-29 Corrected symlink
2017-08-29 Changed ENABLE to ENABLE_CLK due to correction in ENABLE generation
2017-08-29 Current project settings
2017-08-29 Footprints re-assigned
2017-08-29 Another rebuild, WIP
2017-08-29 FCP cart WIP
2017-08-29 Work in progress, pinout for gamepak flat cable
2017-08-29 50 pins FCP connector in progress
2017-08-30 20 pin FCP for gamepak power lines
2017-08-30 Adjusted gamepak FCP connections, joystick port
2017-08-30 Proper Molex FCP 50 pin layout for gamepak
2017-08-30 Better layout, work in progress
2017-08-30 Wire wire line
2017-08-30 Decoupling C134 added
2017-08-30 Sub-sheets title text increased
2017-08-30 Laying around, cleanier look
2017-08-31 Outer layer GND fillzone added, TODO re-plot gerber files
2017-08-31 This in use instead of TUMD2
2017-08-31 Not in use anymore
2017-08-31 D2 footprint changed to 0805
2017-09-03 Done, ERC passed, just need additional confirmation
2017-09-03 Routing in progress, almost completed
2017-09-03 CART EDGE CIC have been made bi-directional to satisfy ERC in rcp-cart schematics
2017-09-03 Completed, to do checks
2017-09-04 Via for stitching power zones
2017-09-04 No waste logo local copy
2017-09-04 PCB look
2017-09-04 Updated PCB look
2017-09-04 Fabricatin files
2017-09-04 Better description
2017-09-04 Pictures added
2017-09-04 RDRAM edge, PLL, PIF, LC125 and most decoupling capacitors aligned
2017-09-04 not sure, actually...
2017-09-05 CART FLAT CABLE mirrored
2017-09-06 More alignments
2017-09-06 Not in use any more
2017-09-06 DC input
2017-09-06 PQ7VZ5 LDO added
2017-09-06 Wrong footprint
2017-09-06 New power input connector
2017-09-06 3D shape for DC input
2017-09-06 C37 VTERM local decoupling added
2017-09-06 R36 and C144 are moved to peripherials sheet
2017-09-07 More alignments and tracks
2017-09-07 More RCP tracks alignments
2017-09-07 CR17 added
2017-09-07 CPU to RCP routing completed
2017-09-08 Verified against physical slot
2017-09-08 Fixing in progress for new CART EDGE footprint
2017-09-09 Most of tracks are tuned down to 0.2mm, updated design rules
2017-09-09 Started to route CPU power wiring
2017-09-09 RCP power wiring is done, todo clock enable
2017-09-10 Basic layout finished, to do checks and tune ups
2017-09-10 Rev.3
2017-09-10 Fabrication files
2017-09-10 Updated with Core Board picture, fixed other boards pictures
2017-09-10 Moved to now more appropriate place
2017-09-12 New fabrication file
2017-09-12 VTERM moved to inner 3V3 layer, added few GND stitch vias, board silkscreen signature
2017-09-13 STEP variant
2017-09-14 STEP source from Molex website
2017-09-16 3D shapes for FreeCAD-PCB mod
2017-09-16 Boards assembly file
